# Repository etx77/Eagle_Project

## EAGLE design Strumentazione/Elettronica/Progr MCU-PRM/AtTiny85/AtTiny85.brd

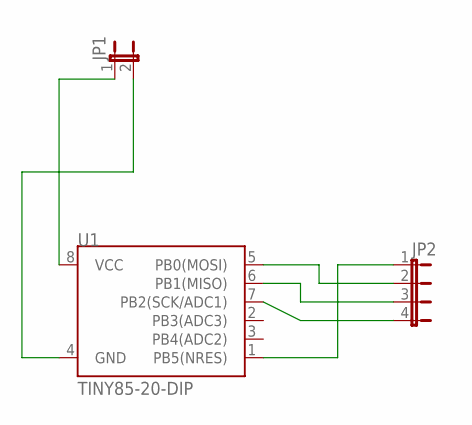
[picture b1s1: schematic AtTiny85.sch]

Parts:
JP1: JP1E; JP1
JP2: JP4E; JP4
U1: TINY85-20-DIP; DIP08

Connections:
unnamed: JP1.1, U1.8 (VCC)
unnamed: JP1.2, U1.4 (GND)
unnamed: JP2.1, U1.1 (PB5(NRES))
unnamed: JP2.2, U1.5 (PB0(MOSI))
unnamed: JP2.3, U1.6 (PB1(MISO))
unnamed: JP2.4, U1.7 (PB2(SCK/ADC1))

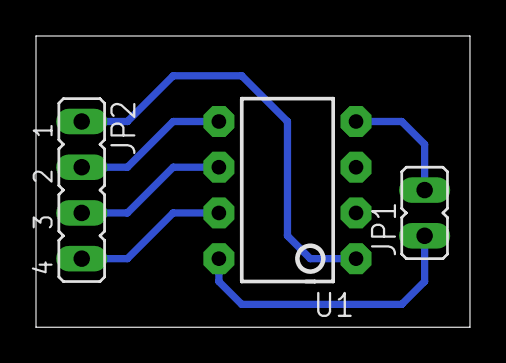
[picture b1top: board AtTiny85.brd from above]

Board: 2 copper layers, 24.1 x 16.2 mm, 3 parts (0 on the bottom side), 6 nets.

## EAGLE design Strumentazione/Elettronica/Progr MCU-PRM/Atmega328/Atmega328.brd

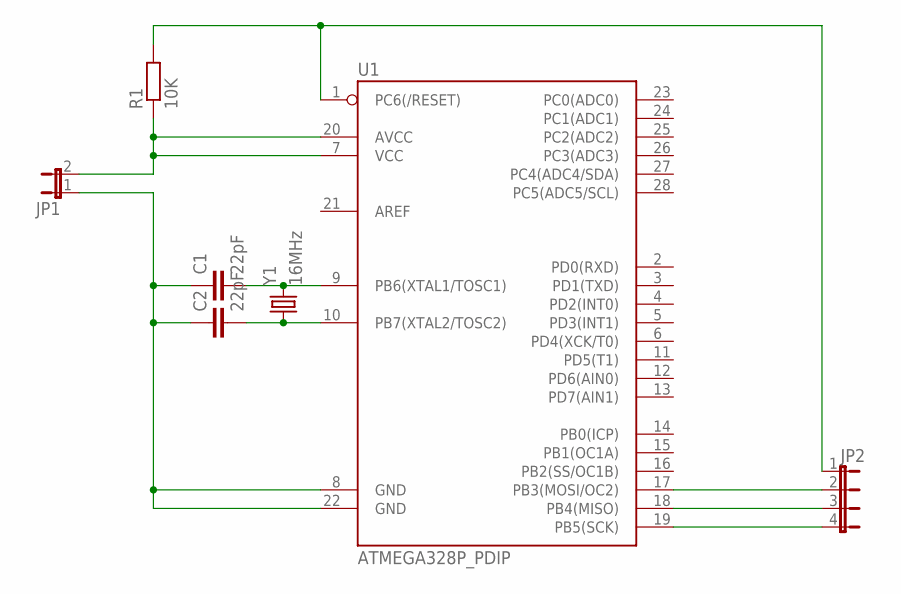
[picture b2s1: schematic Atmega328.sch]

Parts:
C1, C2: 22pF; C025-024X044
JP1: JP1E; JP1
JP2: JP4E; JP4
R1: 10K; 0207/15
U1: ATMEGA328P_PDIP; DIL28-3
Y1: 16MHz; HC49US

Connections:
unnamed: C1.2, U1.9 (PB6(XTAL1/TOSC1)), Y1.2
unnamed: C2.2, U1.10 (PB7(XTAL2/TOSC2)), Y1.1
unnamed: C1.1, C2.1, JP1.1, U1.8 (GND), U1.22 (GND)
unnamed: JP1.2, R1.1, U1.7 (VCC), U1.20 (AVCC)
unnamed: JP2.1, R1.2, U1.1 (PC6(/RESET))
unnamed: JP2.2, U1.17 (PB3(MOSI/OC2))
unnamed: JP2.3, U1.18 (PB4(MISO))
unnamed: JP2.4, U1.19 (PB5(SCK))

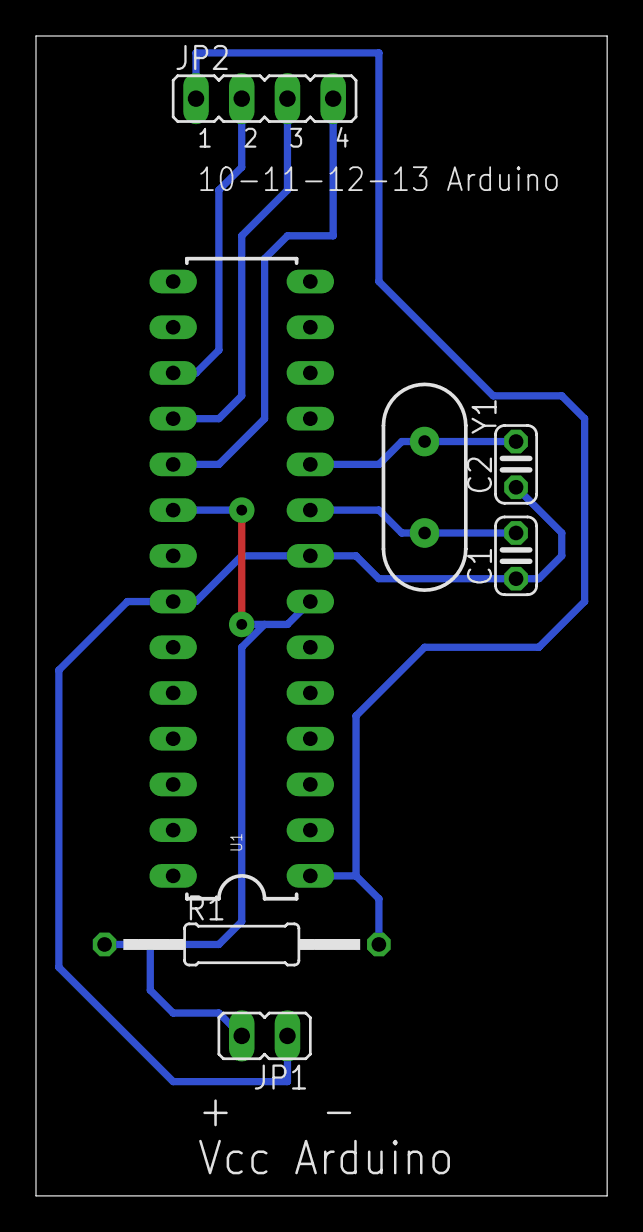
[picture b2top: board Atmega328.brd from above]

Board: 2 copper layers, 31.7 x 64.4 mm, 7 parts (0 on the bottom side), 8 nets.

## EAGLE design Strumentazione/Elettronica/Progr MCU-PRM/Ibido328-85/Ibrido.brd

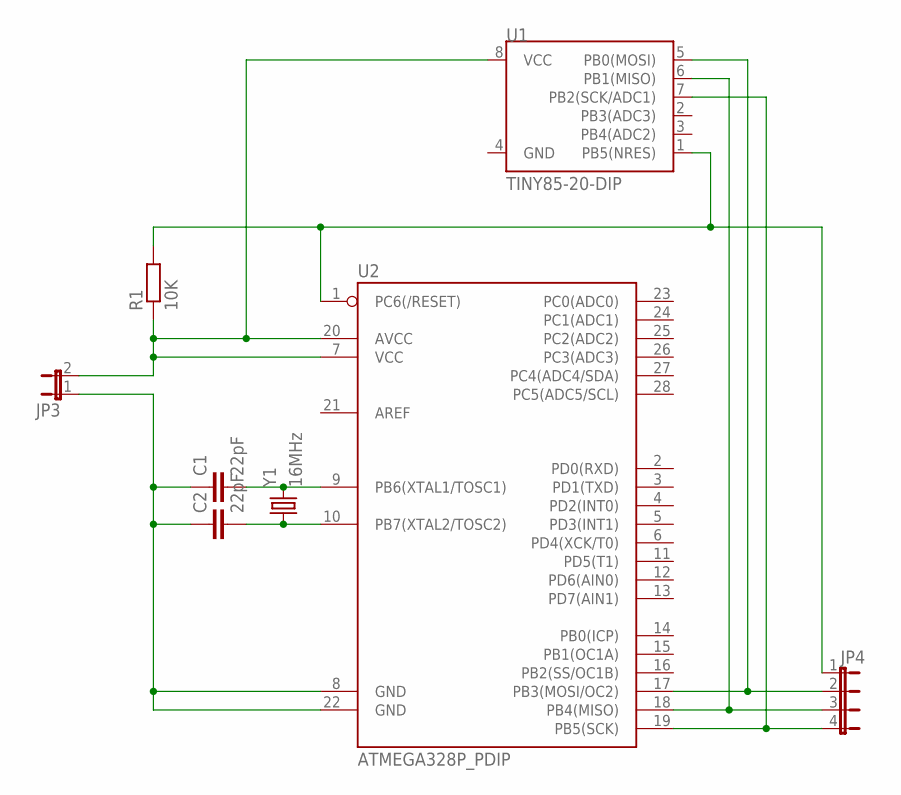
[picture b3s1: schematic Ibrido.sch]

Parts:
C1, C2: 22pF; C025-024X044
JP3: JP1E; JP1
JP4: JP4E; JP4
R1: 10K; 0207/15
U1: TINY85-20-DIP; DIP08
U2: ATMEGA328P_PDIP; DIL28-3
Y1: 16MHz; HC49US

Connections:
unnamed: JP4.2, U1.5 (PB0(MOSI)), U2.17 (PB3(MOSI/OC2))
unnamed: JP4.1, R1.2, U1.1 (PB5(NRES)), U2.1 (PC6(/RESET))
unnamed: JP4.3, U1.6 (PB1(MISO)), U2.18 (PB4(MISO))
unnamed: C1.2, U2.9 (PB6(XTAL1/TOSC1)), Y1.2
unnamed: C2.2, U2.10 (PB7(XTAL2/TOSC2)), Y1.1
unnamed: C1.1, C2.1, JP3.1, U2.8 (GND), U2.22 (GND)
unnamed: JP3.2, R1.1, U1.8 (VCC), U2.7 (VCC), U2.20 (AVCC)
unnamed: JP4.4, U1.7 (PB2(SCK/ADC1)), U2.19 (PB5(SCK))

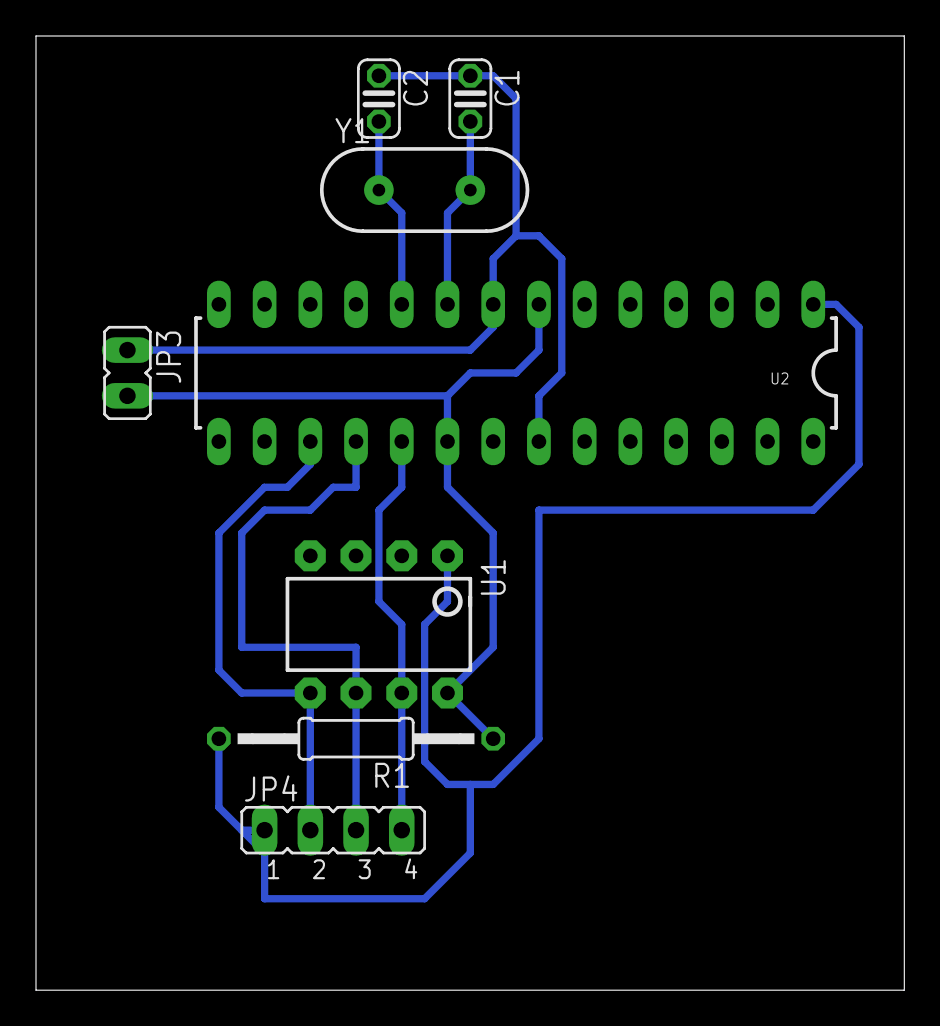
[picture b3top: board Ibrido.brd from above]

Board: 2 copper layers, 48.2 x 53.0 mm, 8 parts (0 on the bottom side), 8 nets.

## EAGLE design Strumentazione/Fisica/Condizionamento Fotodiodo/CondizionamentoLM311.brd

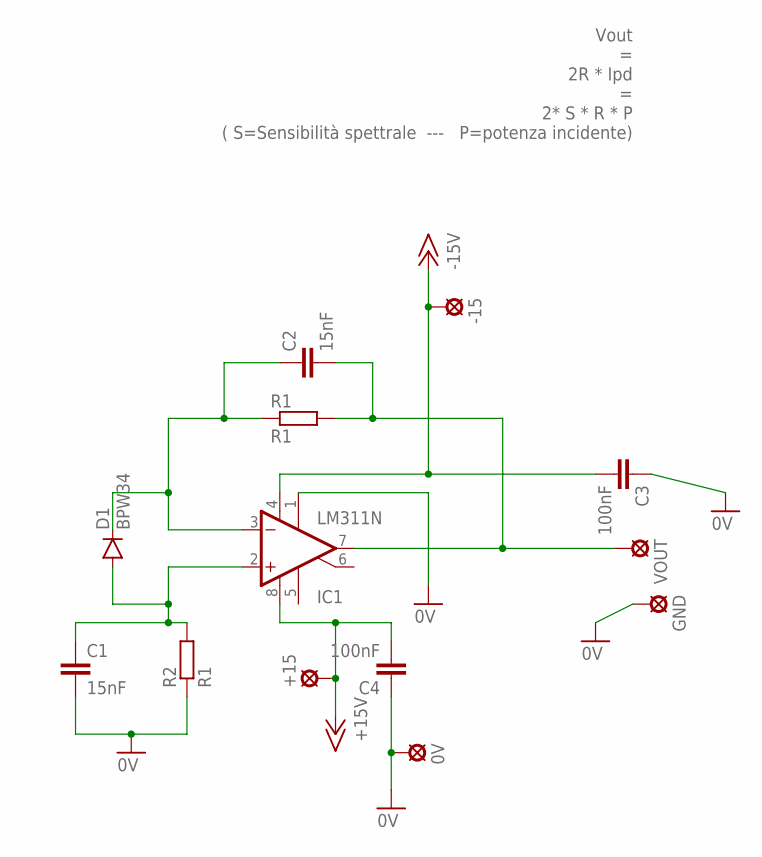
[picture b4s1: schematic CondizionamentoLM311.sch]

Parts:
0V: 0V; LSP10
+15: +15; LSP10
-15: -15; LSP10
C1, C2: 15nF; C050-024X044
C3, C4: 100nF; C050-024X044
D1: BPW34
GND: 0V; LSP10
IC1: LM311N; DIL08
R1, R2: R1; 0207/10
VOUT: Vout; LSP10

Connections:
0V: 0V.MP, C1.2, C3.1, C4.1, GND.MP, IC1.1 (GND), R2.1
+15V: +15.MP, C4.2, IC1.8 (V+)
-15V: -15.MP, C3.2, IC1.4 (V-)
unnamed: C2.2, IC1.7 (OUT), R1.2, VOUT.MP
unnamed: C1.1, D1.P$1 (A), IC1.2 (+IN), R2.2
unnamed: C2.1, D1.P$2 (C), IC1.3 (-IN), R1.1

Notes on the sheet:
Vout = 2R * Ipd = 2* S * R * P ( S=Sensibilità spettrale --- P=potenza incidente)

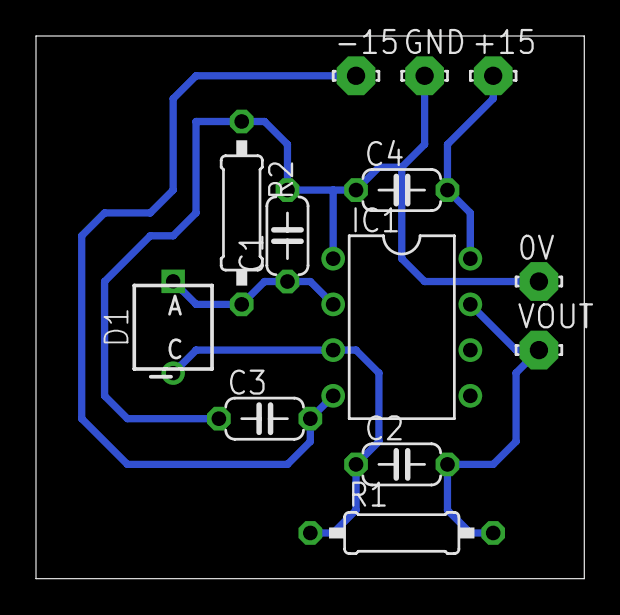
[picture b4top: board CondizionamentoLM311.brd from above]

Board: 2 copper layers, 30.5 x 30.1 mm, 13 parts (0 on the bottom side), 6 nets.

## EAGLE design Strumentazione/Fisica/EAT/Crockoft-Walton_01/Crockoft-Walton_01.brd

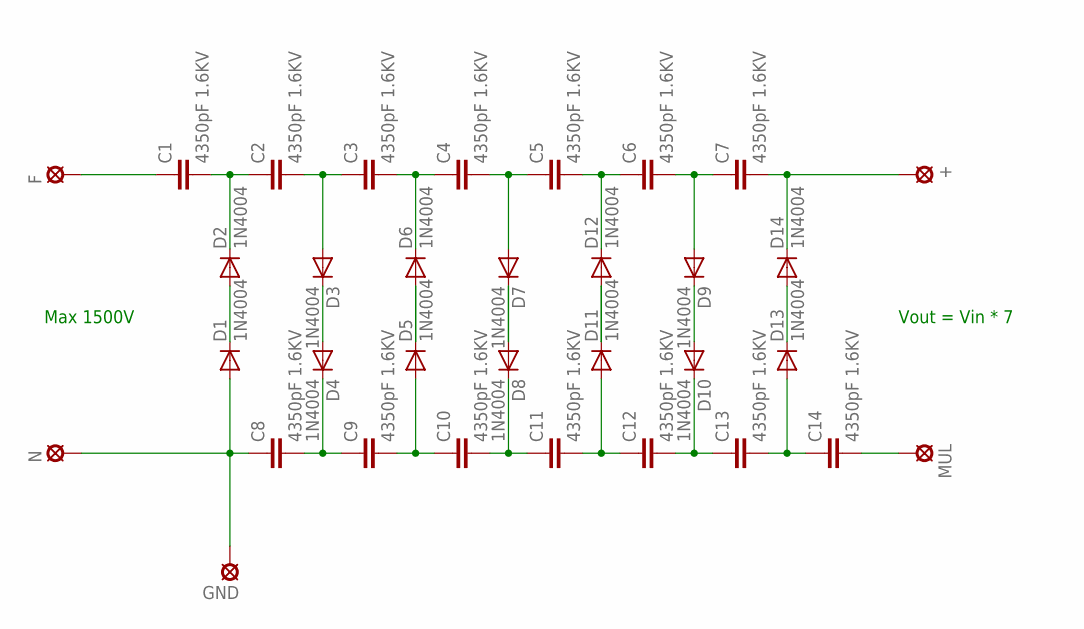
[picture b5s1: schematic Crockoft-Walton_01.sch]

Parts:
+: LSP13
C1, C2, C3, C4, C5, C6, C7, C8, C9, C10, C11, C12, C13, C14: 4350pF 1.6KV; C225-074X268
D1, D2, D3, D4, D5, D6, D7, D8, D9, D10, D11, D12, D13, D14: 1N4004; DO41-10
F: LSP13
GND: LSP13
MUL: LSP13
N: LSP13

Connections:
unnamed: C1.2, C2.1, D2.C
unnamed: C2.2, C3.1, D3.A
unnamed: C3.2, C4.1, D6.C
unnamed: C4.2, C5.1, D7.A
unnamed: C5.2, C6.1, D12.C
unnamed: C6.2, C7.1, D9.A
unnamed: C8.2, C9.1, D4.C
unnamed: C9.2, C10.1, D5.A
unnamed: C10.2, C11.1, D8.C
unnamed: C11.2, C12.1, D11.A
unnamed: C12.2, C13.1, D10.C
unnamed: C13.2, C14.1, D13.A
unnamed: D1.C, D2.A
unnamed: D3.C, D4.A
unnamed: D5.C, D6.A
unnamed: D7.C, D8.A
unnamed: D9.C, D10.A
unnamed: D11.C, D12.A
unnamed: D13.C, D14.A
unnamed: C8.1, D1.A, GND.MP, N.MP
unnamed: +.MP, C7.2, D14.C
unnamed: C14.2, MUL.MP
unnamed: C1.1, F.MP

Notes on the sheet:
Max 1500V
Vout = Vin * 7

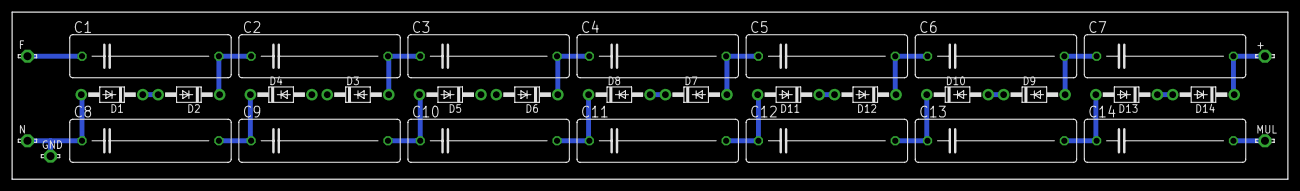
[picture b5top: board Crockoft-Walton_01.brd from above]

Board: 2 copper layers, 210.8 x 27.6 mm, 33 parts (0 on the bottom side), 23 nets.

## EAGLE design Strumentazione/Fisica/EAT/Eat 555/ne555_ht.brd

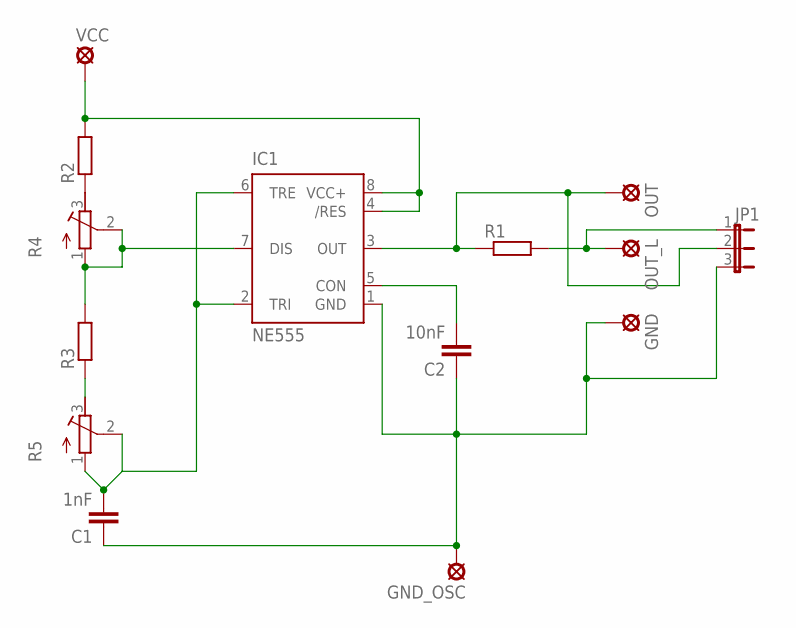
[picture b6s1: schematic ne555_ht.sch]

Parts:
C1: 1nF; C050-024X044
C2: 10nF; C050-024X044
GND: LSP13
GND_OSC: LSP13
IC1: NE555; DIL-08
JP1: JP2E; JP2
OUT: LSP13
OUT_L: LSP13
R1: R-EU_0207/10; 0207/10
R2, R3: R-EU_0207/12; 0207/12
R4, R5: R-TRIMM3339P; RTRIM3339P
VCC: LSP13

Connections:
unnamed: R2.1, R4.3 (E)
unnamed: IC1.4 (/RES), IC1.8 (VCC+), R2.2, VCC.MP
unnamed: C2.2, IC1.5 (CON)
unnamed: C1.1, C2.1, GND.MP, GND_OSC.MP, IC1.1 (GND), JP1.3
unnamed: IC1.3 (OUT), JP1.2, OUT.MP, R1.1
unnamed: JP1.1, OUT_L.MP, R1.2
unnamed: IC1.7 (DIS), R3.2, R4.1 (A), R4.2 (S)
unnamed: R3.1, R5.3 (E)
unnamed: C1.2, IC1.2 (TRI), IC1.6 (TRE), R5.1 (A), R5.2 (S)

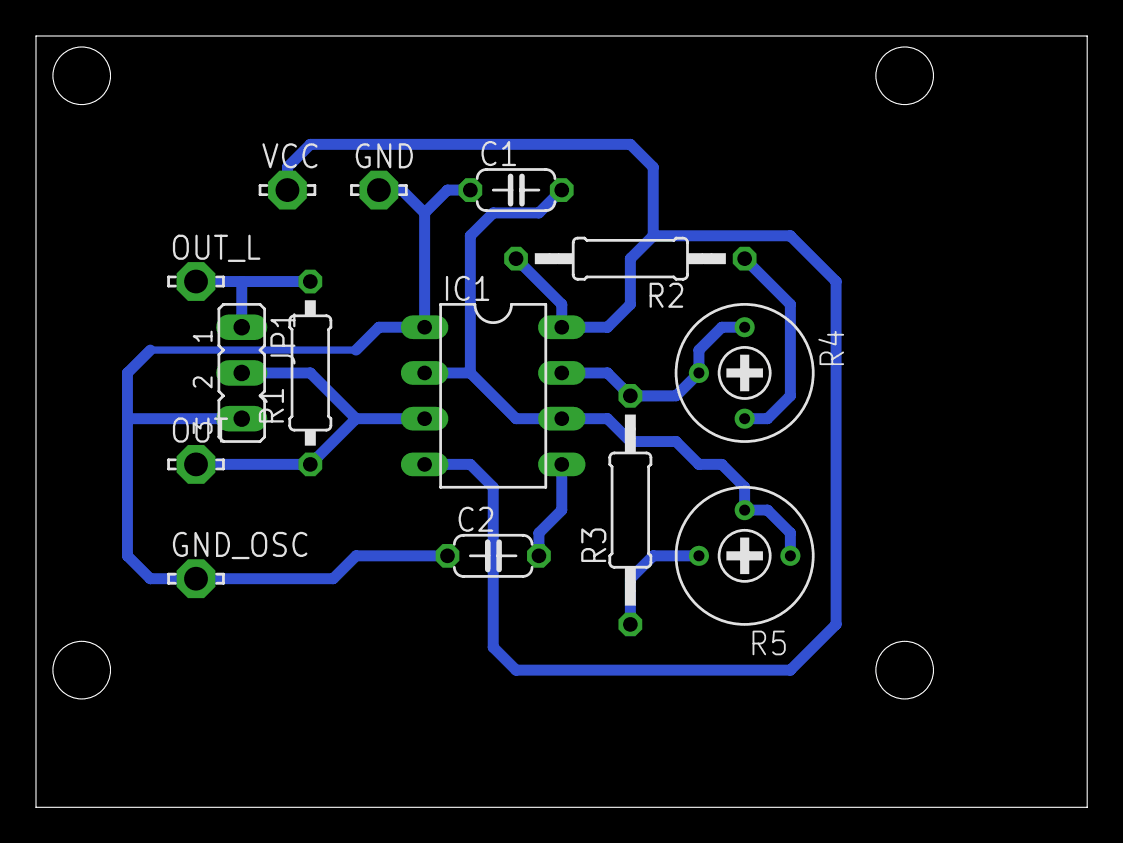
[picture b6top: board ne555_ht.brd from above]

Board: 2 copper layers, 58.4 x 42.9 mm, 14 parts (0 on the bottom side), 9 nets.

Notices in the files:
parts and their libraries:
SparkFun-DigitalIC: Licensing: Creative Commons ShareAlike 4.0 International - https://creativecommons.org/licenses/by-sa/4.0
